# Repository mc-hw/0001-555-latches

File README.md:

# 555-based latches (0001)

## Description

The circuit contains of three latches: astable, monostable and bistable. Each of them is built around a separate 555
integrated circuit with configurable parameters.

The astable latch is built around integrated circuit U1. Potentiometers RV1 and RV2, together with resistors R1, R2
and capacitor C1 regulate the frequency and duty cycle of the `ASTBL_OUT` output signal according to
[555 Timer Calculator](https://www.build-electronic-circuits.com/circuit-calculator-conversion/555-timer-calculator/).
The frequency range is 1Hz-1kHz. The `ASTBL_OUT` signal is provided to screw connector J2. The state of `ASTBL_OUT`
signal is visualised with D1 LED.

The bistable latch is build around integrated circuit U2. Pushing SW1 button triggers high output state of `BSTBL_OUT`
signal. Pushing SW2 button triggers low output state of `BSTBL_OUT` signal. The `BSTBL_OUT` signal is provided to screw
connector J3. The state of `BSTBL_OUT` signal is visualised with D2 LED.

The monostable latch is build around integrated circuit U3. Potentiometer RV3, together with resistor R6 and capacitor
C4 regulate the pulse duration of the `MSTBL_OUT` output signal according to
[555 Timer Calculator](https://www.build-electronic-circuits.com/circuit-calculator-conversion/555-timer-calculator/).
The pulse is triggered by pushing SW3 button. The pulse duration range is 25ms-25s. The `MSTBL_OUT` signal is provided
to screw connector J4. The state of `MSTBL_OUT` signal is visualised with D3 LED.

The maximal output current of each output signal is ~15mA (input voltage/1000).

## Assembly

The circuit should be assembled on a single-sided, THT printed circuit board.

## Running

The device should be powered with 5-15VDC provided to J1 `DC_IN` (center-positive DC jack 2.1/5.5).

After providing the voltage all output signals should be available (observe LED visualisations).

## Bill of Materials

| Reference            | Qty | Value     |
|----------------------|-----|-----------|
| C1                   | 1   | 470nF     |
| C2,C3,C5             | 3   | 10nF      |
| C4                   | 1   | 22uF      |
| D1                   | 1   | RED       |
| D2                   | 1   | GREEN     |
| D3                   | 1   | YELLOW    |
| J1                   | 1   | DC_IN     |
| J2                   | 1   | ASTBL_OUT |
| J3                   | 1   | BSTBL_OUT |
| J4                   | 1   | MSTBL_OUT |
| R1,R2,R6,R7,R8,R9    | 6   | 1k        |
| R3,R4,R5,R10,R11,R12 | 6   | 10k       |
| RV1,RV2,RV3          | 3   | 1M        |
| SW1,SW2,SW3          | 3   | SW_Push   |
| U1,U2,U3             | 3   | NE555P    |

## References

- [555 Timer Tutorial](https://www.build-electronic-circuits.com/555-timer/)
- [555 Timer Calculator](https://www.build-electronic-circuits.com/circuit-calculator-conversion/555-timer-calculator/)
- [KiCad Schematic Editor documentation](https://docs.kicad.org/9.0/en/eeschema/eeschema.html)
- [KiCad YouTube tutorial 1](https://youtube.com/playlist?list=PL3bNyZYHcRSUhUXUt51W6nKvxx2ORvUQB&si=8JaQM5K1sOJ2W4WG)
- [KiCad YouTube tutorial 2](https://youtube.com/playlist?list=PLEBQazB0HUyQ5YJSdCBb79orXaR3Uk5vm&si=labIkKh_z3xuK7w0)
- [KiCad YouTube tutorial 3](https://www.youtube.com/playlist?list=PLUOaI24LpvQPls1Ru_qECJrENwzD7XImd)
- Preparing PCBs using thermotransfer (Youtube [PL]):
    - [1](https://www.youtube.com/watch?v=IV76AiosMgo)
    - [2](https://www.youtube.com/watch?v=NjvKmZZtHUM)
    - [3](https://www.youtube.com/watch?v=1L4GrPDR9TE) - great effect
    - [4](https://www.youtube.com/watch?v=EEXGR3g5FFA) - interesting way of positioning chalk paper
    - [5](https://www.youtube.com/watch?v=SyNOZ-EPTKQ) - interesting drill technique
    - [6](https://www.youtube.com/watch?v=qdos-b2LzrI)
- Preparing PCBs using chemotransfer (Youtube):
    - [1](https://www.youtube.com/watch?v=XGvP0mEEXu8) - Interesting method with acetone/alcohol transfer
    - [2](https://www.youtube.com/watch?v=cVhSCEPINpM&t=17s) - Interesting method with polish remover transfer
    - [3](https://www.youtube.com/watch?v=wvU2yyfH-XE) - Applying solder mask
    - [4](https://www.youtube.com/watch?v=IfhOYhjXLDg) - Applying solder mask

## Implementation

### Breadboard testing

Circuits were tested using breadboard before assembly. Each latch was tested separately.

Testing site:

555 integrated circuit in the bread board:

Minimal astable latch configuration resistance measurement:

Maximal astable latch configuration resistance measurement:

Astable latch testing circuit ready:

Last astable latch continuity testing before providing power:

Astable latch maximal frequency measurement:

Astable latch minimal frequency measurement:

Astable latch maximal current measurement:

Bistable latch testing:

Monostable latch testing:

### PCB preparation

#### Mark 1

The printout for the first instance of PCB was printed on the page from magazine.

The surface was prepared for transfer using cleaning milk, sand paper (1000, wet) and isopropanol.

Next the printout was stuck to the copper using paper tape and doused with Moisturising polish remover.

The remaining of paper was removed in warm water with dish soup

The result was far from perfect, so the decision was to start again.
The traces were removed using nitro:

#### Mark 2

The traces were printed on the glossy side of thermotransfer paper. Unfortunately, the result was bad. Another try was
printing on the magazine page, this time more glossy.
**For the future, in KiCad print dialog, try 'Drill Marks: Small mark'.**

The surface was again cleaned with Acetone.

The printout was fine cut this time and stuck to the surface.

The paths were transferred using Moisturising polish remover again.

The paper did not come out easily, so it was put into warm water with dish soap.

The traces required corrections, which were done using corrector and permanent marker.

The etcher was prepared according to instructions.

PCB was etched in 50 degrees Celsius.

Toner was removed with Nitro. (**For the future: Use capital letters on custom text. Apply text also in the mask
layer**).

The drilling of mounting points was performed using hand drill. **For the future: table drill is a must.**

The front side of PCB was skimmed with Isopropanol.

The silk screen was printed on the glossy leaflet and aligned to the mounting point holes.

The silk screen was transferred using Acetone/Isopropanol solution (50/50).

The result was miserable, so the layer was removed with Acetone.

Another try was printing on the magazine page (the same as for back side, Mk2). The following layers were printed:
F.Silkscreen, User.Comments (for mounting points visibility), Edge.Cuts, F.Courtyard.

The silkscreen was transferred using Moisturising polish remover. The result was OK, but not perfect.
**For the future: Use capital letters for custom text**.

The paper was removed with vinegar/water solution (30/70).

The PCB was skimmed using Isopropanol and dried with hot air before solder mask application.

The blue _Relief_ solder mask was applied using plastic card.

The F.Mask layer with 'No drill mark' option was used as a stencil. **For the future: Place printed side of the stencil
up, multiple layers. 2 hours could be too long (mask was hard even under the stencil). Use matt film.**

The solder mask was hardened using UV diode light (~2h), pressed with a glass dish, but the effect was far from
expected, the dish is not perfectly flat (**For the future: try pressing with glass**).

The solder mask was removed from fields using Acetone (best so far, Isopropanol also is promising). However, mask didn't
get of fields where it was thickest. Fields were also covered with toner (**For the future: Place printed side of the
stencil up.**) and was only partially removed. It was unfortunately not equally thick (**For the future: try pressing
with glass**).

On the front side solder mask was applied using brush. The effect was much better than using plastic card.
Although, the layer was too thick. It was also not equally thick.

The remaining, not hardened solder mask was removed using Acetone. Silkscreen was surprisingly well visible.

Sandpaper (1000) was used to remove covered fields. Unfortunately, it also removed large part of solder mask itself.

The front side was covered with solder mask again. This time with brush but the bubbles were removed through the film
using plastic card.

Solder mask was hardened for ~1 hour.

After first hardening solder mask was cleaned up and left for hardening again.

Another solder mask application was done after pressing double stencil printed up with acryl plexi. The surface was
cleaned up first with Isopropanol.

The mask was cleaned up with Acetone. **For the future: try shorter hardening. The mask was hard to remove.**

After removing the mask, the surface was hardened again.

The front side was de-glossed using sandpaper (grade 3000). The effect was OK, but using mat film is better.

The silkscreen was transferred using chalk paper and iron.

The effect exceeded expectations.

Half of fields were tinned before drilling. Seems like a good idea to tin first.

Half of fields were punched before drilling. **For the future: avoid punching, try only on biggest fields.**

Drilling was performed using table drill.

After cutting edges, the final effect was as below. **For the future: try cutting on the initial phase of PCB
production.**

#### Mark 3

- For Mark 3 a copper piece (~120 x ~100 mm) was cut. The edges were smoothed with file.
- The surface (both sides) were cleaned with cleaning milk, sand paper (1000), Acetone and Isopropanol.
- The copper layer was printed on a big piece of glossy page from magazine, 'Small drill mark' option selected.
- The paths were transferred using Moisturising polish remover with paper wrapped around copper as envelope (seems worse
  than fine-cut piece).
- The paths were corrected with marker, corrector and scalpel.
- The holes for mounting points were drilled after etching, before toner removal.
- After etching toner was removed using Acetone.
- The PCB was cleaned with Isopropanol and dried with hot air (270 degrees Celsius).
- The front side of PCB was covered with tape before solder mask application.
- _Mechanic_ solder mask was applied using a plastic card through a stencil printed down on mat film. On top of it
  another stencil, printed down on glossy film was placed. It was pressed between two acryl panes and left for 10
  minutes to spread evenly.
- The first UV hardening took 30 minutes, half by half, from 10cm.
- The fields were removed with Isopropanol. Unfortunately, the result was poor. Longer hardening needed? Also the layer
  was too thick.

#### Mark 4

- For Mark 4 a copper piece (~120 x ~100 mm) was cut. The edges were smoothed with a file.
- The surface (both sides) were cleaned with cleaning milk, sand paper (1000), Acetone and Isopropanol.
- The copper layer was printed on a big piece of glossy page from magazine, 'Small drill mark' option selected.
- The paths were transferred using Moisturising polish remover with paper fine cut and stuck to copper using paper tape.
- The PCB was fine-cut, the edges were smoothed with a file and sandpaper (grade 150). The file was a bad idea.
- The paths were corrected with marker and scalpel.
- The holes for mounting points were drilled after etching.
- After etching toner was removed using Acetone.
- The entire PCB (both sides, edges) was smoothed with sandpaper (grade 1000) and cleaned with Nitro (outperforms even
  Acetone).
- _Mechanic_ solder mask was applied using a plastic card through a stencil printed down on mat film. On top of it
  another stencil, printed down on glossy film was placed. It was pressed between two acryl panes.
- The first UV hardening took 45 minutes, equally covered by light, from 20cm.
- The fields were removed with Isopropanol. They were also corrected by Acetone, but it seems to be too aggressive.
  Unfortunately, the result was poor. Also, the layer was too thick.
- The missing parts of back side solder mask was covered with brush and toothpick.
- Fields were tinned before drilling.

#### Mark 5

- For Mark 5 a copper piece (~120 x ~100 mm) was cut. The edges were smoothed with a file. Seems to be a bad idea,
  solder mask is fragile and breaks, it's better to fine-cut before etching.
- The surface (both sides) were cleaned with cleaning milk, sand paper (1000), Acetone and Isopropanol.
- The copper layer was printed on a big piece of glossy page from magazine, 'No drill mark' option selected.
- The paths were transferred using Moisturising polish remover with paper fine cut and stuck to copper using paper tape.
- The PCB was fine-cut, the edges were smoothed with a file and sandpaper (grade 150). The file was a bad idea.
- The paths were corrected with marker and scalpel.
- The holes for mounting points were drilled before etching. Seems to be a good idea, holes were smoother after etching.
- After etching toner was removed using Acetone.
- The entire PCB (both sides, edges) was smoothed with sandpaper (grade 1000) and cleaned with Acetone.
- Both sides were painted with a colophony dissolved in Nitro (seems like a bad idea, stencil got stuck).
- _Mechanic_ solder mask was applied using a plastic card through a stencil printed down on mat film (printed twice). On
  top of it another stencil, printed down on glossy film was placed. It was pressed between two acryl panes.
- The first UV hardening took 90 minutes (each corner first, 15 minutes, central later, 30 minutes).
- The fields were removed with Isopropanol.
- The front side was cleaned with Isopropanol before solder mask application. The back side was covered with tape.
- _Mechanic_ solder mask was applied to the front side using a plastic card through a matt film. It was pressed between
  two acryl panes, but the top glass was removed before hardening.
- The UV hardening took 1 hour (each corner first, 10 minutes, central later, 20 minutes).
- The film was removed millimeter by millimeter, starting with corners, holding with a plastic card.
- The result was OK, but it was better when the hardening time was longer.
- Both sides were again painted with a colophony dissolved in Nitro

#### Mark 6

- For Mark 6 a copper piece (~120 x ~100 mm) was cut. The edges were smoothed with a file.
- The surface (both sides) were cleaned with cleaning milk, sand paper (1000), Acetone and Isopropanol.
- The copper layer was printed on a big piece of glossy page from magazine, 'No drill mark' option selected.
- The paths were transferred using Moisturising polish remover with paper fine cut and stuck to copper using paper tape.
- The PCB was fine-cut, the edges were smoothed with a file and sandpaper (grade 150). The file was a bad idea.
- The paths were corrected with marker and scalpel.
- The holes for mounting points were drilled before etching. Seems to be a good idea, holes were smoother after etching.
- After etching toner was removed using Acetone.
- The entire PCB (both sides, edges) was smoothed with sandpaper (grade 1000) and cleaned with Nitro (outperforms even
  Acetone).
- The front side of PCB was covered with tape before solder mask application.
- _Mechanic_ solder mask was applied using a plastic card through a stencil printed down on mat film (printed twice). It
  was pressed between two acryl panes, but the top glass was removed before hardening.
- The UV hardening took 1 hour 15 minutes (each corner first, 15 minutes, central later, 15 minutes).
- The stencil was removed millimeter by millimeter, starting with corners, holding with a plastic card. The fields were
  removed with Isopropanol. The result was pretty OK. The fields were smaller than expected, try shortening the
  hardening time.
- The front side was cleaned with Isopropanol before solder mask application. The back side was covered with tape.
- _Mechanic_ solder mask was applied to the front side using a plastic card through a matt film. It was pressed between
  two acryl panes, but the top glass was removed before hardening.
- The UV hardening took 1.5 hour (each corner first, 20 minutes, central later, 30 minutes).
- The stencil was removed millimeter by millimeter, starting with corners, holding with a plastic card. The fields were
  removed with Isopropanol. The result was pretty good. Could consider shorter hardening.
- The silkscreen was printed (twice) on chalk paper and transferred with iron.
- Corners were again covered with solder mask, where it was missing. The result was OK, but try another layer of solder
  mask.
- Fields were tinned before drilling.

## PCB ordering

Gerber files should be generated for each PCB manufacturer individually, every manufacturer have a different
requirements for Gerber files. There is no general solution which could be generated upfront for each manufacturer.

Only manufacturers, who allow initiating orders using Gerber/KiCAD files were selected.

Considered manufacturers:

- [Satland Prototype (pl)](https://www.prototypy.com/sites_pcbplugins/pcborder/58)
- [Laskar (pl)](https://laskar.com.pl/): Minimal order - 20 dm2, PLN 365 net for single-sided board.
- [Margol (pl)](https://www.fabrykapcb.pl/index.html)
- [EMS Electronix (pl)](https://www.ems-elektronix.com/zapytania-ofertowe/#formularz-ofertowy)
- [ts (pl)](https://tspcb.pl/zamow-wycen/)
- [PCB Way (ch)](https://www.pcbway.com/)
- [multi-cb (de)](https://portal.multi-circuit-boards.eu/)

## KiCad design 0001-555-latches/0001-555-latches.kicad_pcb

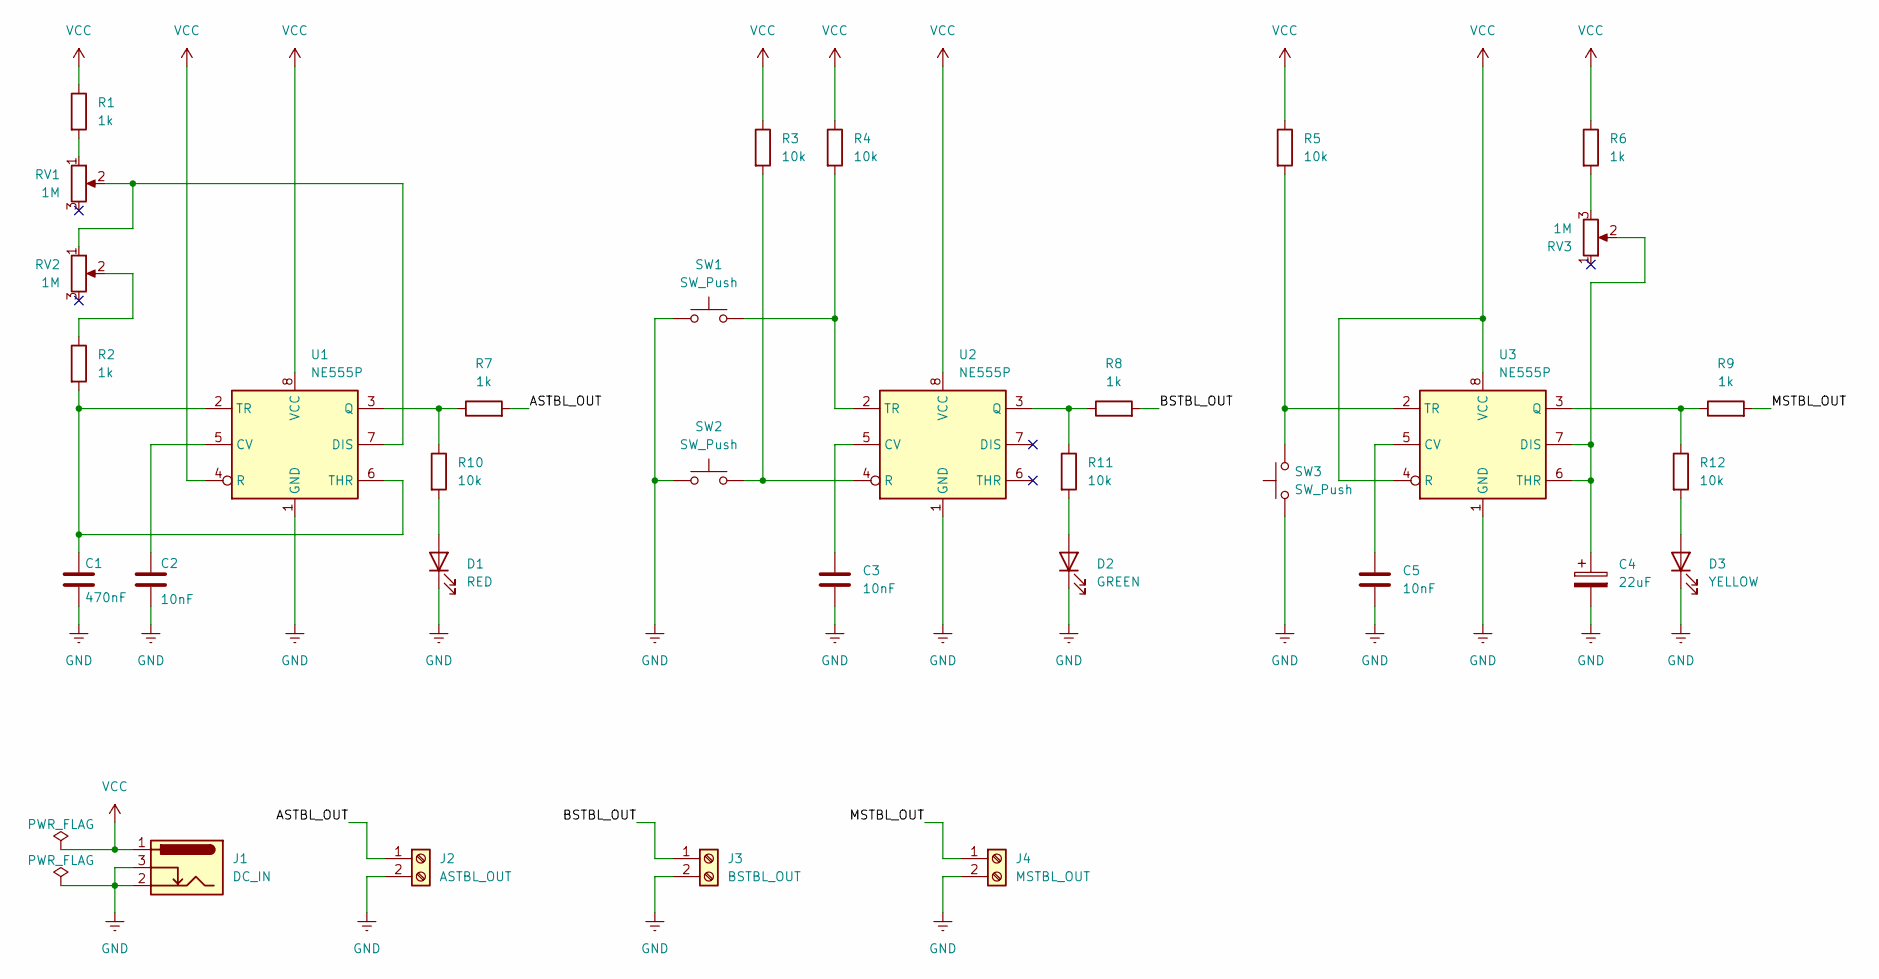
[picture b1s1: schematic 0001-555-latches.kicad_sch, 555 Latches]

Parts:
C1: 470nF; C_Rect_L7.0mm_W3.5mm_P5.00mm
C2, C3, C5: 10nF; C_Rect_L7.0mm_W3.5mm_P5.00mm
C4: 22uF; CP_Radial_D5.0mm_P2.00mm
D1: RED; LED_D5.0mm
D2: GREEN; LED_D5.0mm
D3: YELLOW; LED_D5.0mm
J1: DC_IN; BarrelJack_Horizontal
J2: ASTBL_OUT; TerminalBlock_4Ucon_1x02_P3.50mm_Horizontal
J3: BSTBL_OUT; TerminalBlock_4Ucon_1x02_P3.50mm_Horizontal
J4: MSTBL_OUT; TerminalBlock_4Ucon_1x02_P3.50mm_Horizontal
R1, R2, R6, R7, R8, R9: 1k; R_Axial_DIN0207_L6.3mm_D2.5mm_P7.62mm_Horizontal
R3, R4, R5, R10, R11, R12: 10k; R_Axial_DIN0207_L6.3mm_D2.5mm_P7.62mm_Horizontal
RV1, RV2, RV3: 1M; Potentiometer_Runtron_RM-065_Vertical
SW1, SW2, SW3: SW_Push; SW_PUSH_6mm_H4.3mm
U1, U2, U3: NE555P; DIP-8_W7.62mm_Socket_LongPads

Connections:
/ASTBL_OUT: J2.1, R7.2
/BSTBL_OUT: J3.1, R8.2
/MSTBL_OUT: J4.1, R9.2
GND: C1.2, C2.2, C3.2, C4.2, C5.2, D1.1 (K), D2.1 (K), D3.1 (K), J1.2, J1.3, J2.2, J3.2, J4.2, SW1.1, SW2.1, SW3.1, U1.1 (GND), U2.1 (GND), U3.1 (GND)
unnamed: D1.2 (A), R10.2
unnamed: D2.2 (A), R11.2
unnamed: D3.2 (A), R12.2
unnamed: R1.2, RV1.1
unnamed: R2.1, RV2.2
unnamed: R6.2, RV3.3
unnamed: C2.1, U1.5 (CV)
unnamed: RV1.2, RV2.1, U1.7 (DIS)
unnamed: R7.1, R10.1, U1.3 (Q)
unnamed: C1.1, R2.2, U1.2 (TR), U1.6 (THR)
unnamed: C3.1, U2.5 (CV)
unnamed: R8.1, R11.1, U2.3 (Q)
unnamed: R3.2, SW2.2, U2.4 (R)
unnamed: R4.2, SW1.2, U2.2 (TR)
unnamed: C5.1, U3.5 (CV)
unnamed: C4.1, RV3.2, U3.6 (THR), U3.7 (DIS)
unnamed: R9.1, R12.1, U3.3 (Q)
unnamed: R5.2, SW3.2, U3.2 (TR)
VCC: J1.1, R1.1, R3.1, R4.1, R5.1, R6.1, U1.4 (R), U1.8 (VCC), U2.8 (VCC), U3.4 (R), U3.8 (VCC)

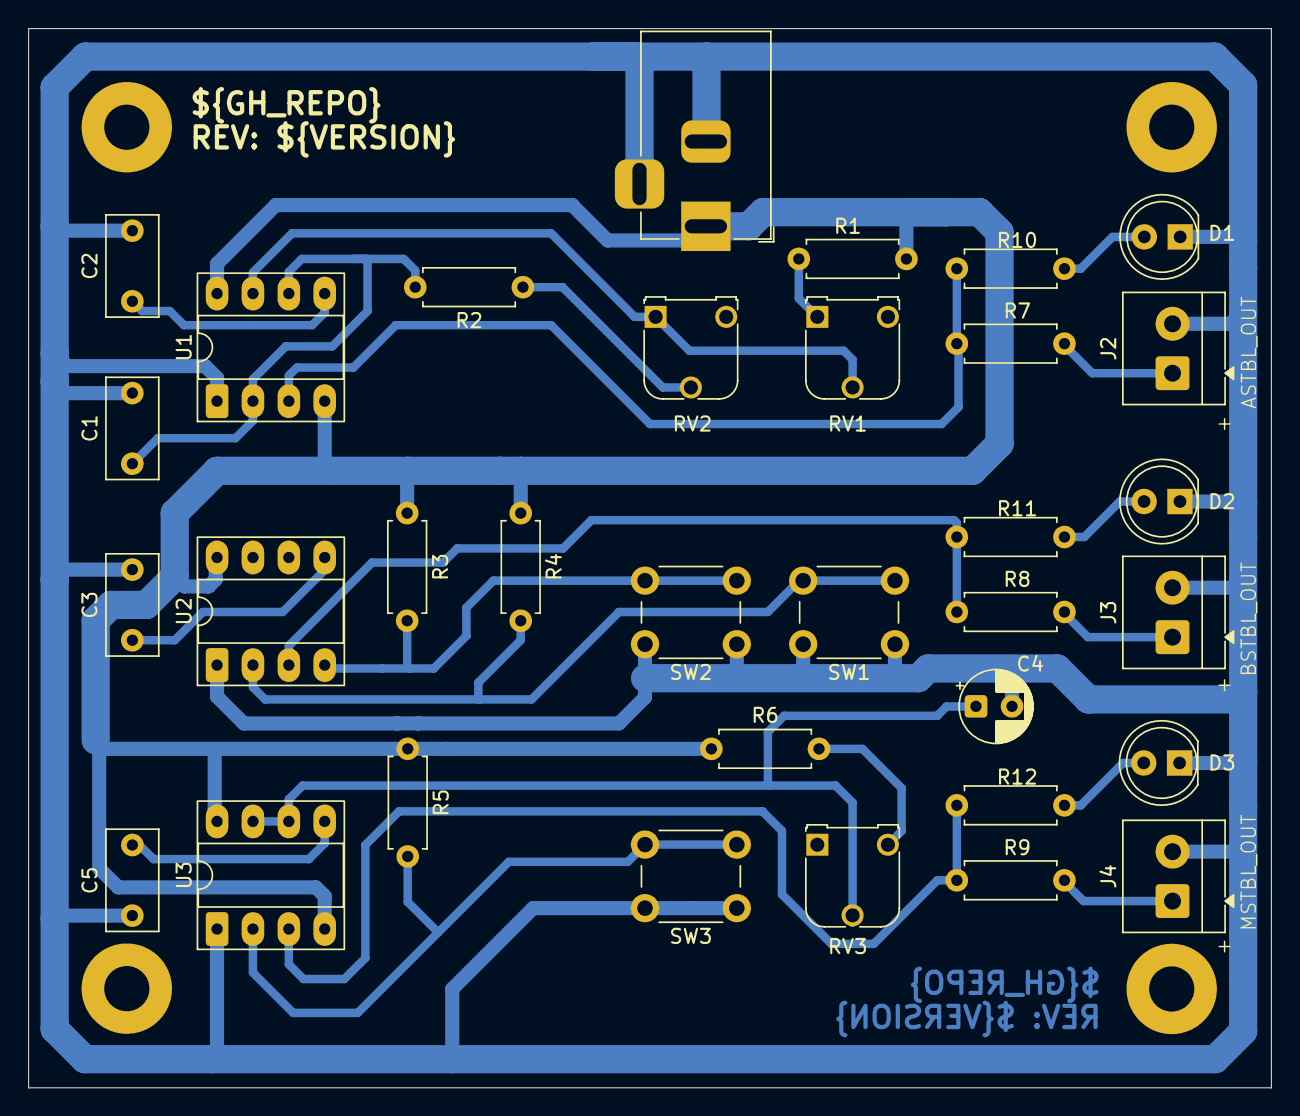
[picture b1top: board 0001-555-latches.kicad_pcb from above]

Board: 2 copper layers, 88.0 x 75.0 mm, 37 parts (0 on the bottom side), 23 nets.

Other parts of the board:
MNT1, MNT2, MNT3, MNT4: MountingHole_3.2mm_M3_Pad

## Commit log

2025-10-05 Initial schematics, astable, bistable
2025-10-06 Monostable latch schematics
2025-10-06 Schematics validation
2025-10-07 Elements values
2025-10-07 Update values and symbols of monostable capacitor
2025-10-08 Improve schematics layout
2025-10-08 Update version
2025-10-08 Fixes after tutorials
2025-10-10 Update potentiometers leads, replace junctions
2025-10-10 Ignore backups
2025-10-10 Workspace cleanup
2025-10-11 Documentation template
2025-10-11 Provide documentation
2025-10-11 Add schematic
2025-10-11 Photorelation
2025-10-11 PCB layout and gerber placeholders
2025-10-11 Fix typos
2025-10-11 Update document structure
2025-10-11 Documentation updates
2025-10-11 Update images
2025-10-11 Update assembly and running sections
2025-10-12 Documentation (#2)
    * Documentation template
    * Add schematic
    * Provide documentation
    * Photorelation
    * Fix typos
    * Update document structure
2025-10-13 footprints
2025-10-13 Fix typo
2025-10-14 First PCB drafts
2025-10-14 All PCB connections
2025-10-15 Replace DC_IN screw connector with DC jack
2025-10-15 PCB compression
2025-10-15 Optimizing tracks
2025-10-15 PCB labels (copper/silk)
2025-10-15 Closing PCB
2025-10-15 Validation
2025-10-15 Tracks optimisation
2025-10-15 PCB layout corrections
2025-10-15 Add PCB layout to documentation
2025-10-16 Update tracing
2025-10-16 Update PCB image
2025-10-16 Move copper description
2025-10-16 Re-scale PCB image
2025-10-16 Traces spacing corrections
2025-10-17 Pcb layout (#3)
    * footprints
    * Fix typo
    * First PCB drafts
    * All PCB connections
    * Replace DC_IN screw connector with DC jack
    * PCB compression
2025-10-17 Update PCB
2025-10-18 PCB ordering candidates
2025-10-18 Update PCB (#4)
    * Update PCB
    * PCB ordering candidates
    ---------
2025-10-18 Resolve todos
2025-10-23 Update GH organisation in PCB
2025-10-23 Correcting files
2025-10-23 Fix formatting
2025-10-24 Implementation (#5)
    * Update GH organisation in PCB
    * Correcting files
    * Fix formatting
    * Fix typo
    ---------
2025-10-25 Mark 1
2025-10-25 Mark2 - photorelation
2025-10-25 Mark 2 - relation
2025-10-25 Solder mask conclusion
2025-10-25 Solder mask conclusions
2025-10-26 Solder mask continuation
2025-10-26 Small corrections
2025-10-26 Solder mask name
2025-10-26 Mark 2 solder mask
2025-10-26 Change formatting
2025-10-27 Pcb production (#6)
    * Mark 1
    * Mark2 - photorelation
    * Mark 2 - relation
    * Solder mask conclusion
    * Solder mask conclusions
    * Solder mask continuation
2025-10-30 Finishing PCB mk2
2025-10-30 Correction
2025-10-31 Pcb mk2 (#7)
    * Finishing PCB mk2
    * Correction
    * Correction
    ---------
2025-10-31 Update labels on PCB
2025-10-31 Mk 3, 4, 5, 6
2025-10-31 Mark 3
2025-11-01 Mk 4
2025-11-02 Mark 6
2025-11-03 Mk6 - solder mask finished
2025-11-03 Mk 4, 5, 6 finished
2025-11-04 Mk 3,4,5,6 final photos
2025-11-05 Pcb mk3,4,5,6 (#8)
    * Update labels on PCB
    * Mk 3, 4, 5, 6
    * Mark 3
    * Mk 4
    * Mark 6
    * Mk6 - solder mask finished
